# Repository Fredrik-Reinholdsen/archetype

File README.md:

# Archetype

A compact System on Module (SOM) for audio processing and DSP.
It features 6-layer, 5x3 cm PCB, a powerful 550 MHz STM32H7 micro-controller with additional peripherals such as a high fidelity audio CODEC,
SDRAM and flash memory.

The board has two mezzanine connectors on the back, one for analog signals and one for digital.
Many of the STM32 peripherals are wired to and accesible via the mezzanine connectors, including SPI, I2C, UART, CAN, ADC inputs.

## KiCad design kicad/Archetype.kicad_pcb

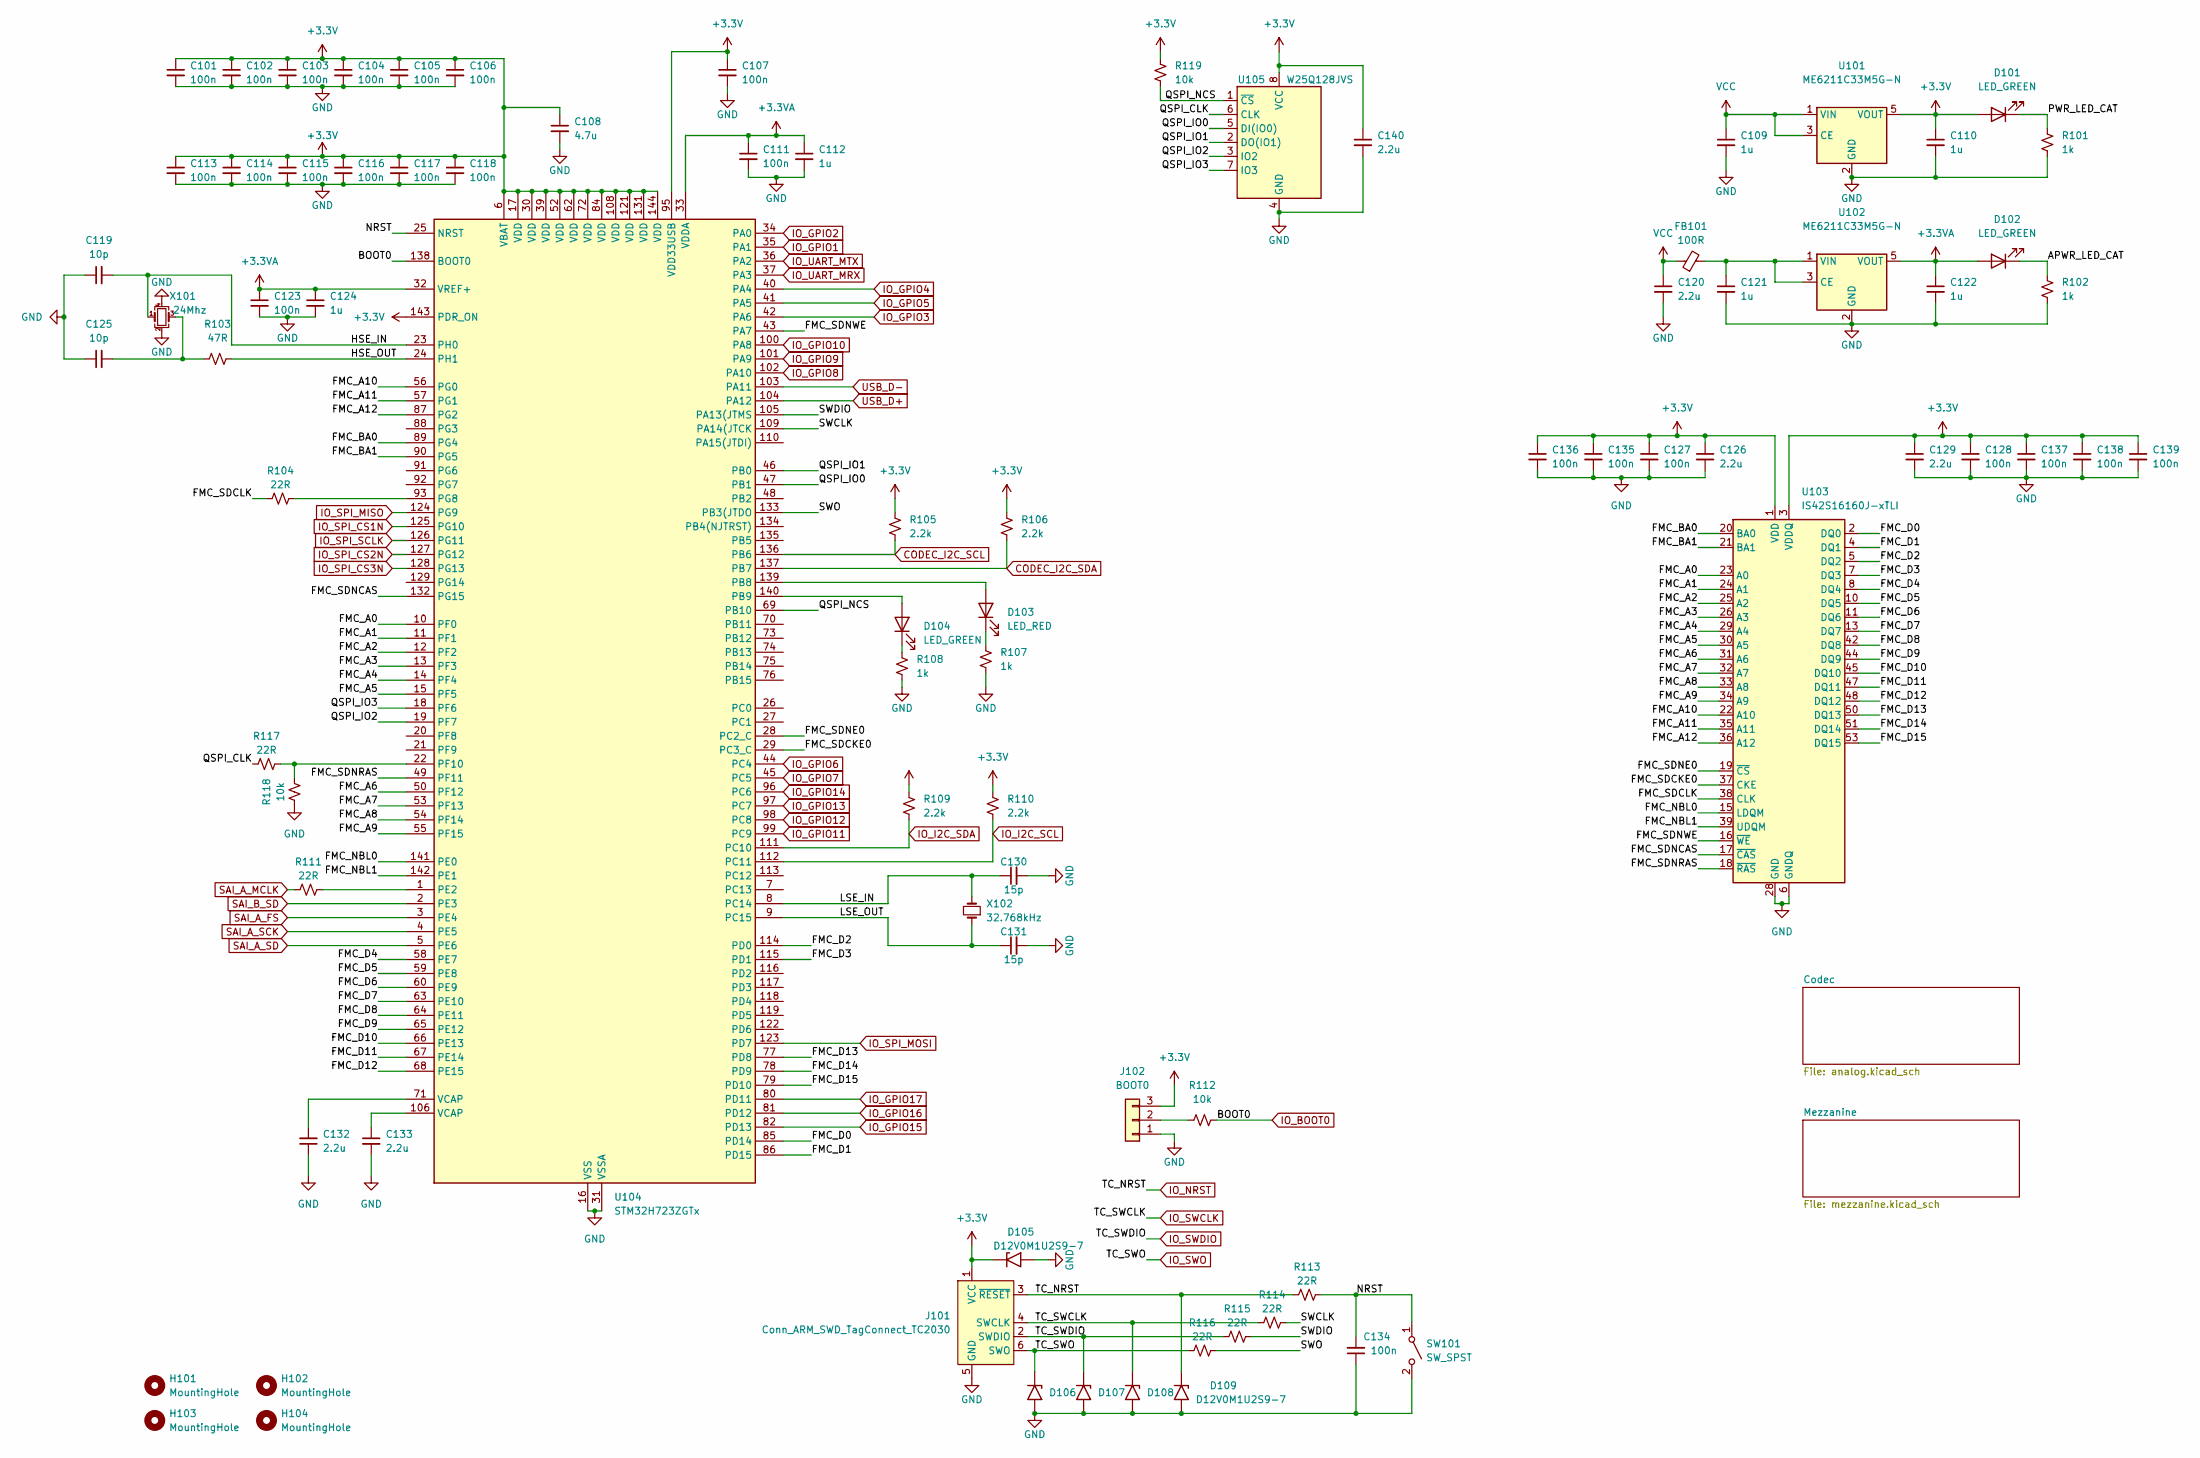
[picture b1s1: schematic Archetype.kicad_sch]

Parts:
C101, C102, C103, C104, C105, C106, C107, C111, C113, C114, C115, C116, C117, C118, C123, C127, C128, C134, C135, C136, C137, C138, C139: 100n; C_0402_1005Metric
C108: 4.7u; C_0402_1005Metric
C109, C110, C112, C121, C122, C124: 1u; C_0402_1005Metric
C119, C125: 10p; C_0603_1608Metric
C120, C126, C129, C132, C133, C140: 2.2u; C_0402_1005Metric
C130, C131: 15p; C_0603_1608Metric
D101, D102, D104: LED_GREEN; LED_0805_2012Metric
D103: LED_RED; LED_0805_2012Metric
D105, D106, D107, D108, D109: D12V0M1U2S9-7; D_SOD-923
FB101: 100R; R_0805_2012Metric
H101, H102, H103, H104: MountingHole; MountingHole_2.2mm_M2_DIN965
J101: Conn_ARM_SWD_TagConnect_TC2030; Tag-Connect_TC2030-IDC-FP_2x03_P1.27mm_Vertical
J102: BOOT0; PinSocket_1x03_P2.54mm_Vertical
R101, R102, R107, R108: 1k; R_0402_1005Metric
R103: 47R; R_0402_1005Metric
R104, R111, R113, R114, R115, R116, R117: 22R; R_0402_1005Metric
R105, R106, R109, R110: 2.2k; R_0402_1005Metric
R112, R118, R119: 10k; R_0402_1005Metric
SW101: SW_SPST; SPST_TS-1187A-B-A-B
U101, U102: ME6211C33M5G-N; SOT-23-5
U103: IS42S16160J-xTLI; TSOP-II-54_22.2x10.16mm_P0.8mm
U104: STM32H723ZGTx; LQFP-144_20x20mm_P0.5mm
U105: W25Q128JVS; SOIC-8_5.23x5.23mm_P1.27mm
X101: 24Mhz; Crystal_SMD_3225-4Pin_3.2x2.5mm
X102: 32.768kHz; SMD_3215-2Pin

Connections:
+3.3V: C101.1, C102.1, C103.1, C104.1, C105.1, C106.1, C107.1, C108.1, C110.1, C113.1, C114.1, C115.1, C116.1, C117.1, C118.1, C126.1, C127.1, C128.1, C129.1, C135.1, C136.1, C137.1, C138.1, C139.1, C140.1, D101.2 (A), D105.1 (A1), J101.1 (VCC), J102.3, R105.1, R106.1, R109.1, R110.1, R119.1, U101.5 (VOUT), U103.1 (VDD), U103.3 (VDDQ), U103.9 (VDDQ), U103.14 (VDD), U103.27 (VDD), U103.43 (VDDQ), U103.49 (VDDQ), U104.6 (VBAT), U104.17 (VDD), U104.30 (VDD), U104.39 (VDD), U104.52 (VDD), U104.62 (VDD), U104.72 (VDD), U104.84 (VDD), U104.95 (VDD33USB), U104.108 (VDD), U104.121 (VDD), U104.131 (VDD), U104.143 (PDR_ON), U104.144 (VDD), U105.8 (VCC); also elsewhere on the board
+3.3VA: C111.1, C112.1, C122.1, C123.1, C124.1, D102.2 (A), U102.5 (VOUT), U104.32 (VREF+), U104.33 (VDDA); also elsewhere on the board
/APWR_LED_CAT: D102.1 (K), R102.1
/FMC_A0: U103.23 (A0), U104.10 (PF0)
/FMC_A1: U103.24 (A1), U104.11 (PF1)
/FMC_A2: U103.25 (A2), U104.12 (PF2)
/FMC_A3: U103.26 (A3), U104.13 (PF3)
/FMC_A4: U103.29 (A4), U104.14 (PF4)
/FMC_A5: U103.30 (A5), U104.15 (PF5)
/FMC_A6: U103.31 (A6), U104.50 (PF12)
/FMC_A7: U103.32 (A7), U104.53 (PF13)
/FMC_A8: U103.33 (A8), U104.54 (PF14)
/FMC_A9: U103.34 (A9), U104.55 (PF15)
/FMC_A10: U103.22 (A10), U104.56 (PG0)
/FMC_A11: U103.35 (A11), U104.57 (PG1)
/FMC_A12: U103.36 (A12), U104.87 (PG2)
/FMC_BA0: U103.20 (BA0), U104.89 (PG4)
/FMC_BA1: U103.21 (BA1), U104.90 (PG5)
/FMC_D0: U103.2 (DQ0), U104.85 (PD14)
/FMC_D1: U103.4 (DQ1), U104.86 (PD15)
/FMC_D2: U103.5 (DQ2), U104.114 (PD0)
/FMC_D3: U103.7 (DQ3), U104.115 (PD1)
/FMC_D4: U103.8 (DQ4), U104.58 (PE7)
/FMC_D5: U103.10 (DQ5), U104.59 (PE8)
/FMC_D6: U103.11 (DQ6), U104.60 (PE9)
/FMC_D7: U103.13 (DQ7), U104.63 (PE10)
/FMC_D8: U103.42 (DQ8), U104.64 (PE11)
/FMC_D9: U103.44 (DQ9), U104.65 (PE12)
/FMC_D10: U103.45 (DQ10), U104.66 (PE13)
/FMC_D11: U103.47 (DQ11), U104.67 (PE14)
/FMC_D12: U103.48 (DQ12), U104.68 (PE15)
/FMC_D13: U103.50 (DQ13), U104.77 (PD8)
/FMC_D14: U103.51 (DQ14), U104.78 (PD9)
/FMC_D15: U103.53 (DQ15), U104.79 (PD10)
/FMC_NBL0: U103.15 (LDQM), U104.141 (PE0)
/FMC_NBL1: U103.39 (UDQM), U104.142 (PE1)
/FMC_SDCKE0: U103.37 (CKE), U104.29 (PC3_C)
/FMC_SDCLK: R104.2, U103.38 (CLK)
/FMC_SDNCAS: U103.17 (~CAS), U104.132 (PG15)
/FMC_SDNE0: U103.19 (~CS), U104.28 (PC2_C)
/FMC_SDNRAS: U103.18 (~RAS), U104.49 (PF11)
/FMC_SDNWE: U103.16 (~WE), U104.43 (PA7)
/HSE_IN: C119.2, U104.23 (PH0), X101.1
/HSE_OUT: R103.1, U104.24 (PH1)
/LSE_IN: C130.1, U104.8 (PC14), X102.2
/LSE_OUT: C131.1, U104.9 (PC15), X102.1
/NRST: C134.2, R113.2, SW101.1 (A), U104.25 (NRST)
/PWR_LED_CAT: D101.1 (K), R101.1
/QSPI_CLK: R117.2, U105.6 (CLK)
/QSPI_IO0: U104.47 (PB1), U105.5 (DI(IO0))
/QSPI_IO1: U104.46 (PB0), U105.2 (DO(IO1))
/QSPI_IO2: U104.19 (PF7), U105.3 (IO2)
/QSPI_IO3: U104.18 (PF6), U105.7 (IO3)
/QSPI_NCS: R119.2, U104.69 (PB10), U105.1 (~CS)
/SWCLK: R114.2, U104.109 (PA14(JTCK)
/SWDIO: R115.2, U104.105 (PA13(JTMS)
/SWO: R116.2, U104.133 (PB3(JTDO)
CODEC_I2C_SCL: R105.2, U104.136 (PB6); also elsewhere on the board
CODEC_I2C_SDA: R106.2, U104.137 (PB7); also elsewhere on the board
GND: C101.2, C102.2, C103.2, C104.2, C105.2, C106.2, C107.2, C108.2, C109.2, C110.2, C111.2, C112.2, C113.2, C114.2, C115.2, C116.2, C117.2, C118.2, C119.1, C120.2, C121.2, C122.2, C123.2, C124.2, C125.1, C126.2, C127.2, C128.2, C129.2, C130.2, C131.2, C132.1, C133.2, C134.1, C135.2, C136.2, C137.2, C138.2, C139.2, C140.2, D105.2 (A2), D106.2 (A2), D107.2 (A2), D108.2 (A2), D109.2 (A2), J101.5 (GND), J102.1, R101.2, R102.2, R107.2, R108.2, R118.2, SW101.2 (B), U101.2 (GND), U102.2 (GND), U103.6 (GNDQ), U103.12 (GNDQ), U103.28 (GND), U103.41 (GND), U103.46 (GNDQ), U103.52 (GNDQ), U103.54 (GND), U104.16 (VSS), U104.31 (VSSA), U104.38 (VSS), U104.51 (VSS), U104.61 (VSS), U104.83 (VSS), U104.94 (VSS), U104.107 (VSS), U104.120 (VSS), U104.130 (VSS), U105.4 (GND), X101.2, X101.4; also elsewhere on the board
IO_BOOT0: R112.2, U104.138 (BOOT0); also elsewhere on the board
IO_GPIO1: U104.35 (PA1); also elsewhere on the board
IO_GPIO2: U104.34 (PA0); also elsewhere on the board
IO_GPIO3: U104.42 (PA6); also elsewhere on the board
IO_GPIO4: U104.40 (PA4); also elsewhere on the board
IO_GPIO5: U104.41 (PA5); also elsewhere on the board
IO_GPIO6: U104.44 (PC4); also elsewhere on the board
IO_GPIO7: U104.45 (PC5); also elsewhere on the board
IO_GPIO8: U104.102 (PA10); also elsewhere on the board
IO_GPIO9: U104.101 (PA9); also elsewhere on the board
IO_GPIO10: U104.100 (PA8); also elsewhere on the board
IO_GPIO11: U104.99 (PC9); also elsewhere on the board
IO_GPIO12: U104.98 (PC8); also elsewhere on the board
IO_GPIO13: U104.97 (PC7); also elsewhere on the board
IO_GPIO14: U104.96 (PC6); also elsewhere on the board
IO_GPIO15: U104.82 (PD13); also elsewhere on the board
IO_GPIO16: U104.81 (PD12); also elsewhere on the board
IO_GPIO17: U104.80 (PD11); also elsewhere on the board
IO_I2C_SCL: R110.2, U104.112 (PC11); also elsewhere on the board
IO_I2C_SDA: R109.2, U104.111 (PC10); also elsewhere on the board
IO_NRST: D109.1 (A1), J101.3 (~RESET), R113.1; also elsewhere on the board
IO_SPI_CS1N: U104.125 (PG10); also elsewhere on the board
IO_SPI_CS2N: U104.127 (PG12); also elsewhere on the board
IO_SPI_CS3N: U104.128 (PG13); also elsewhere on the board
IO_SPI_MISO: U104.124 (PG9); also elsewhere on the board
IO_SPI_MOSI: U104.123 (PD7); also elsewhere on the board
IO_SPI_SCLK: U104.126 (PG11); also elsewhere on the board
IO_SWCLK: D108.1 (A1), J101.4 (SWCLK), R114.1; also elsewhere on the board
IO_SWDIO: D107.1 (A1), J101.2 (SWDIO), R115.1; also elsewhere on the board
IO_SWO: D106.1 (A1), J101.6 (SWO), R116.1; also elsewhere on the board
IO_UART_MRX: U104.37 (PA3); also elsewhere on the board
IO_UART_MTX: U104.36 (PA2); also elsewhere on the board
unnamed: C125.2, R103.2, X101.3
unnamed: C132.2, U104.71 (VCAP)
unnamed: C133.1, U104.106 (VCAP)
unnamed: D103.2 (A), U104.139 (PB8)
unnamed: D103.1 (K), R107.1
unnamed: D104.2 (A), U104.140 (PB9)
unnamed: D104.1 (K), R108.1
unnamed: J102.2, R112.1
unnamed: C121.1, FB101.2, U102.1 (VIN), U102.3 (CE)
unnamed: R111.1, U104.1 (PE2)
unnamed: R117.1, R118.1, U104.22 (PF10)
unnamed: R104.1, U104.93 (PG8)
SAI_A_FS: U104.3 (PE4); also elsewhere on the board
SAI_A_MCLK: R111.2; also elsewhere on the board
SAI_A_SCK: U104.4 (PE5); also elsewhere on the board
SAI_A_SD: U104.5 (PE6); also elsewhere on the board
SAI_B_SD: U104.2 (PE3); also elsewhere on the board
USB_D+: U104.104 (PA12); also elsewhere on the board
USB_D-: U104.103 (PA11); also elsewhere on the board
VCC: C109.1, C120.1, FB101.1, U101.1 (VIN), U101.3 (CE); also elsewhere on the board

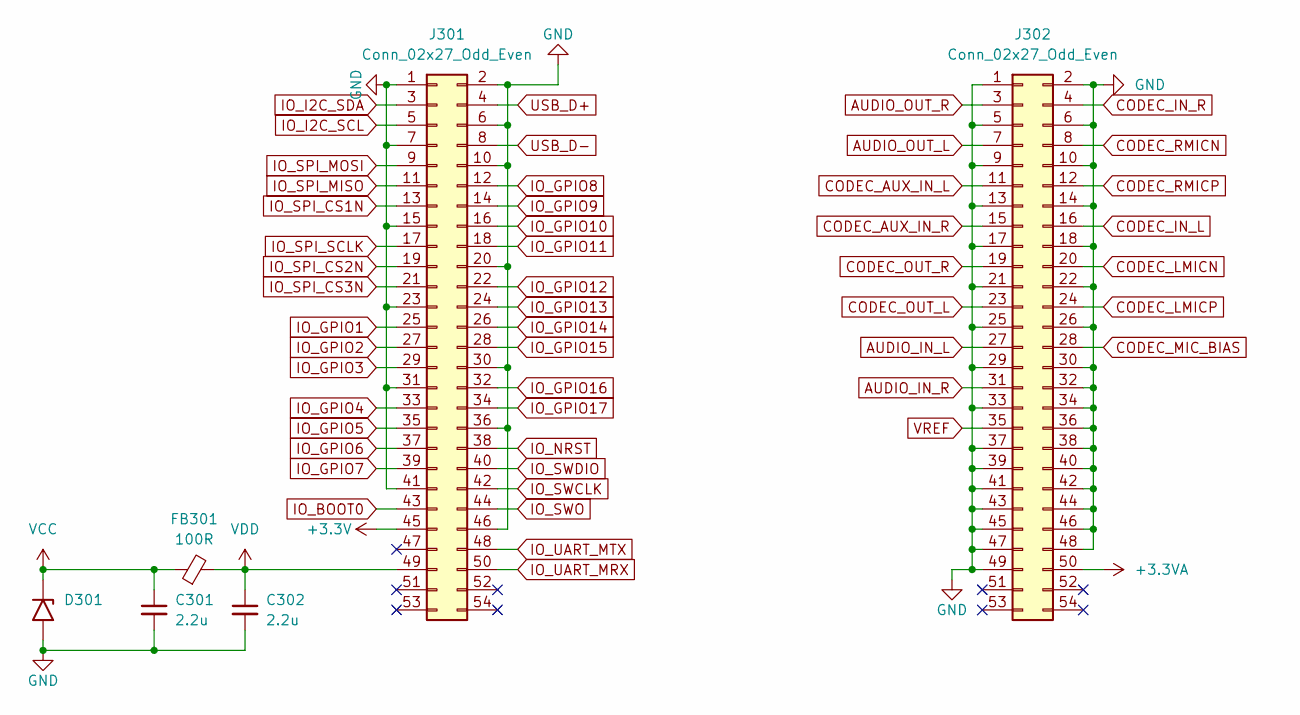
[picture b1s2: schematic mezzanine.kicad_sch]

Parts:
C301, C302: 2.2u; C_0402_1005Metric
D301: D12V0M1U2S9-7; D_SOD-923
FB301: 100R; R_0805_2012Metric
J301, J302: Conn_02x27_Odd_Even; DF40C-50DP-0.4V

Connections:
+3.3V: J301.45; also elsewhere on the board
+3.3VA: J302.50; also elsewhere on the board
AUDIO_IN_L: J302.27; also elsewhere on the board
AUDIO_IN_R: J302.31; also elsewhere on the board
AUDIO_OUT_L: J302.7; also elsewhere on the board
AUDIO_OUT_R: J302.3; also elsewhere on the board
CODEC_AUX_IN_L: J302.11; also elsewhere on the board
CODEC_AUX_IN_R: J302.15; also elsewhere on the board
CODEC_IN_L: J302.16; also elsewhere on the board
CODEC_IN_R: J302.4; also elsewhere on the board
CODEC_LMICN: J302.20; also elsewhere on the board
CODEC_LMICP: J302.24; also elsewhere on the board
CODEC_MIC_BIAS: J302.28; also elsewhere on the board
CODEC_OUT_L: J302.23; also elsewhere on the board
CODEC_OUT_R: J302.19; also elsewhere on the board
CODEC_RMICN: J302.8; also elsewhere on the board
CODEC_RMICP: J302.12; also elsewhere on the board
GND: C301.2, C302.2, D301.2 (A2), J301.1, J301.2, J301.6, J301.7, J301.10, J301.15, J301.20, J301.23, J301.30, J301.31, J301.36, J301.41, J301.46, J302.1, J302.2, J302.5, J302.6, J302.9, J302.10, J302.13, J302.14, J302.17, J302.18, J302.21, J302.22, J302.25, J302.26, J302.29, J302.30, J302.32, J302.33, J302.34, J302.36, J302.37, J302.38, J302.39, J302.40, J302.41, J302.42, J302.43, J302.44, J302.45, J302.46, J302.47, J302.48, J302.49; also elsewhere on the board
IO_BOOT0: J301.43; also elsewhere on the board
IO_GPIO1: J301.25; also elsewhere on the board
IO_GPIO2: J301.27; also elsewhere on the board
IO_GPIO3: J301.29; also elsewhere on the board
IO_GPIO4: J301.33; also elsewhere on the board
IO_GPIO5: J301.35; also elsewhere on the board
IO_GPIO6: J301.37; also elsewhere on the board
IO_GPIO7: J301.39; also elsewhere on the board
IO_GPIO8: J301.12; also elsewhere on the board
IO_GPIO9: J301.14; also elsewhere on the board
IO_GPIO10: J301.16; also elsewhere on the board
IO_GPIO11: J301.18; also elsewhere on the board
IO_GPIO12: J301.22; also elsewhere on the board
IO_GPIO13: J301.24; also elsewhere on the board
IO_GPIO14: J301.26; also elsewhere on the board
IO_GPIO15: J301.28; also elsewhere on the board
IO_GPIO16: J301.32; also elsewhere on the board
IO_GPIO17: J301.34; also elsewhere on the board
IO_I2C_SCL: J301.5; also elsewhere on the board
IO_I2C_SDA: J301.3; also elsewhere on the board
IO_NRST: J301.38; also elsewhere on the board
IO_SPI_CS1N: J301.13; also elsewhere on the board
IO_SPI_CS2N: J301.19; also elsewhere on the board
IO_SPI_CS3N: J301.21; also elsewhere on the board
IO_SPI_MISO: J301.11; also elsewhere on the board
IO_SPI_MOSI: J301.9; also elsewhere on the board
IO_SPI_SCLK: J301.17; also elsewhere on the board
IO_SWCLK: J301.42; also elsewhere on the board
IO_SWDIO: J301.40; also elsewhere on the board
IO_SWO: J301.44; also elsewhere on the board
IO_UART_MRX: J301.50; also elsewhere on the board
IO_UART_MTX: J301.48; also elsewhere on the board
USB_D+: J301.4; also elsewhere on the board
USB_D-: J301.8; also elsewhere on the board
VCC: C301.1, D301.1 (A1), FB301.1; also elsewhere on the board
VDD: C302.1, FB301.2, J301.49
VREF: J302.35; also elsewhere on the board

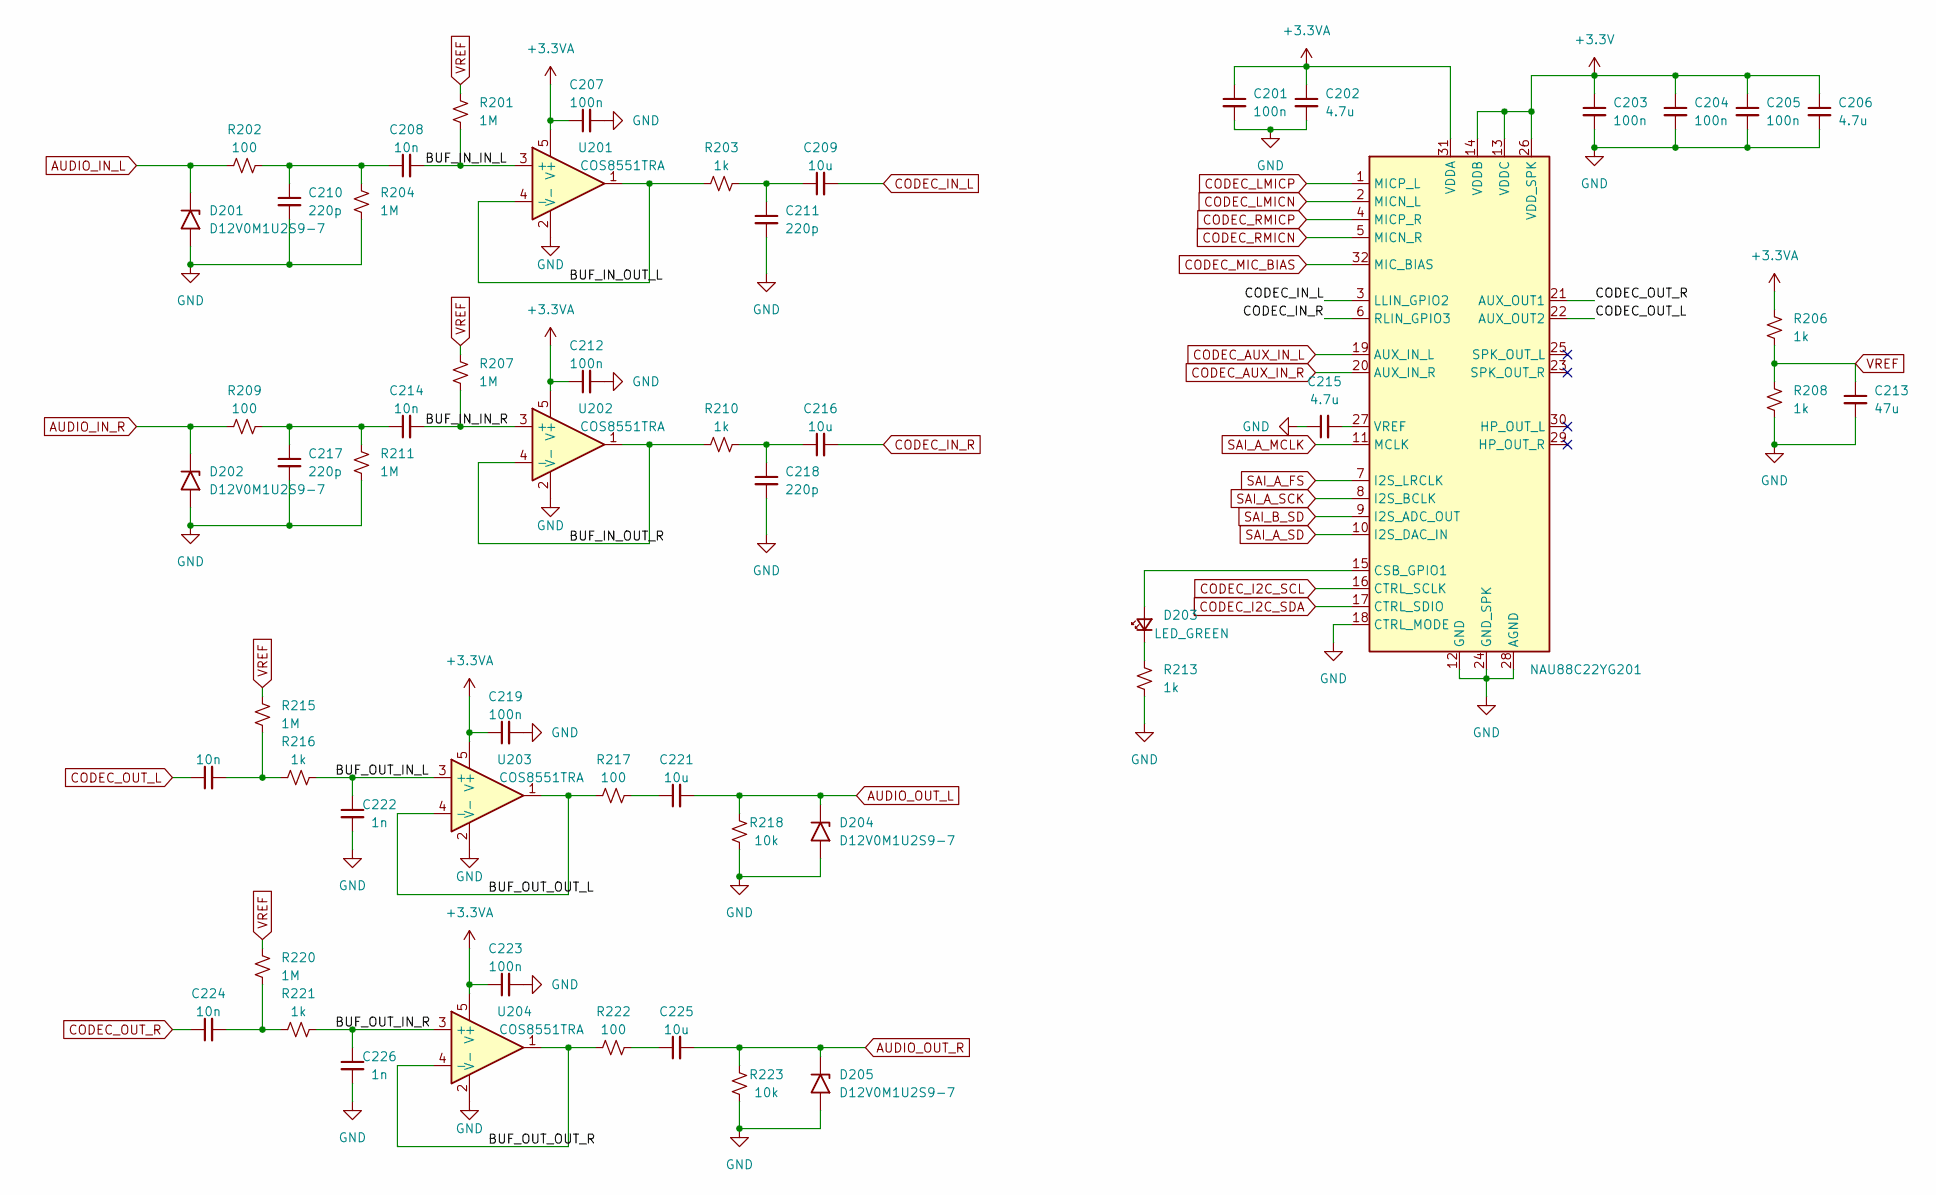
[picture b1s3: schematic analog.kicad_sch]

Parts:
C201, C203, C204, C205, C207, C212, C219, C223: 100n; C_0402_1005Metric
C202, C206, C215: 4.7u; C_0402_1005Metric
C208, C214, C220, C224: 10n; C_0402_1005Metric
C209, C216, C221, C225: 10u; C_0402_1005Metric
C210, C211, C217, C218: 220p; C_0402_1005Metric
C213: 47u; C_0402_1005Metric
C222, C226: 1n; C_0402_1005Metric
D201, D202, D204, D205: D12V0M1U2S9-7; D_SOD-923
D203: LED_GREEN; LED_0805_2012Metric
NAU88C22YG201: VQFN-32-1EP_5x5mm_P0.5mm_EP3.5x3.5mm
R201, R204, R207, R211, R215, R220: 1M; R_0402_1005Metric
R202, R209, R217, R222: 100; R_0402_1005Metric
R203, R206, R208, R210, R213, R216, R221: 1k; R_0402_1005Metric
R218, R223: 10k; R_0402_1005Metric
U201, U202, U203, U204: COS8551TRA; SOT-23-5

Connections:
+3.3V: C203.1, C204.1, C205.1, C206.1, NAU88C22YG201.13 (VDDC), NAU88C22YG201.14 (VDDB), NAU88C22YG201.26 (VDD_SPK); also elsewhere on the board
+3.3VA: C201.1, C202.1, C207.1, C212.1, C219.1, C223.1, NAU88C22YG201.31 (VDDA), R206.2, U201.5 (V+), U202.5 (V+), U203.5 (V+), U204.5 (V+); also elsewhere on the board
/Codec/BUF_IN_IN_L: C208.2, R201.1, U201.3 (+)
/Codec/BUF_IN_IN_R: C214.2, R207.1, U202.3 (+)
/Codec/BUF_IN_OUT_L: R203.2, U201.1, U201.4 (-)
/Codec/BUF_IN_OUT_R: R210.2, U202.1, U202.4 (-)
/Codec/BUF_OUT_IN_L: C222.1, R216.1, U203.3 (+)
/Codec/BUF_OUT_IN_R: C226.1, R221.1, U204.3 (+)
/Codec/BUF_OUT_OUT_L: R217.2, U203.1, U203.4 (-)
/Codec/BUF_OUT_OUT_R: R222.2, U204.1, U204.4 (-)
AUDIO_IN_L: D201.1 (A1), R202.1; also elsewhere on the board
AUDIO_IN_R: D202.1 (A1), R209.1; also elsewhere on the board
AUDIO_OUT_L: C221.2, D204.1 (A1), R218.2; also elsewhere on the board
AUDIO_OUT_R: C225.2, D205.1 (A1), R223.2; also elsewhere on the board
CODEC_AUX_IN_L: NAU88C22YG201.19 (AUX_IN_L); also elsewhere on the board
CODEC_AUX_IN_R: NAU88C22YG201.20 (AUX_IN_R); also elsewhere on the board
CODEC_I2C_SCL: NAU88C22YG201.16 (CTRL_SCLK); also elsewhere on the board
CODEC_I2C_SDA: NAU88C22YG201.17 (CTRL_SDIO); also elsewhere on the board
CODEC_IN_L: C209.2, NAU88C22YG201.3 (LLIN_GPIO2); also elsewhere on the board
CODEC_IN_R: C216.2, NAU88C22YG201.6 (RLIN_GPIO3); also elsewhere on the board
CODEC_LMICN: NAU88C22YG201.2 (MICN_L); also elsewhere on the board
CODEC_LMICP: NAU88C22YG201.1 (MICP_L); also elsewhere on the board
CODEC_MIC_BIAS: NAU88C22YG201.32 (MIC_BIAS); also elsewhere on the board
CODEC_OUT_L: C220.1, NAU88C22YG201.22 (AUX_OUT2); also elsewhere on the board
CODEC_OUT_R: C224.1, NAU88C22YG201.21 (AUX_OUT1); also elsewhere on the board
CODEC_RMICN: NAU88C22YG201.5 (MICN_R); also elsewhere on the board
CODEC_RMICP: NAU88C22YG201.4 (MICP_R); also elsewhere on the board
GND: C201.2, C202.2, C203.2, C204.2, C205.2, C206.2, C207.2, C210.2, C211.2, C212.2, C213.2, C215.1, C217.2, C218.2, C219.2, C222.2, C223.2, C226.2, D201.2 (A2), D202.2 (A2), D204.2 (A2), D205.2 (A2), NAU88C22YG201.12 (GND), NAU88C22YG201.18 (CTRL_MODE), NAU88C22YG201.24 (GND_SPK), NAU88C22YG201.28 (AGND), NAU88C22YG201.33 (GND), R204.1, R208.1, R211.1, R213.2, R218.1, R223.1, U201.2 (V-), U202.2 (V-), U203.2 (V-), U204.2 (V-); also elsewhere on the board
unnamed: C208.1, C210.1, R202.2, R204.2
unnamed: C209.1, C211.1, R203.1
unnamed: C214.1, C217.1, R209.2, R211.2
unnamed: C216.1, C218.1, R210.1
unnamed: C220.2, R215.1, R216.2
unnamed: C221.1, R217.1
unnamed: C224.2, R220.1, R221.2
unnamed: C225.1, R222.1
unnamed: D203.2 (A), NAU88C22YG201.15 (CSB_GPIO1)
unnamed: D203.1 (K), R213.1
unnamed: C215.2, NAU88C22YG201.27 (VREF)
SAI_A_FS: NAU88C22YG201.7 (I2S_LRCLK); also elsewhere on the board
SAI_A_MCLK: NAU88C22YG201.11 (MCLK); also elsewhere on the board
SAI_A_SCK: NAU88C22YG201.8 (I2S_BCLK); also elsewhere on the board
SAI_A_SD: NAU88C22YG201.10 (I2S_DAC_IN); also elsewhere on the board
SAI_B_SD: NAU88C22YG201.9 (I2S_ADC_OUT); also elsewhere on the board
VREF: C213.1, R201.2, R206.1, R207.2, R208.2, R215.2, R220.2; also elsewhere on the board

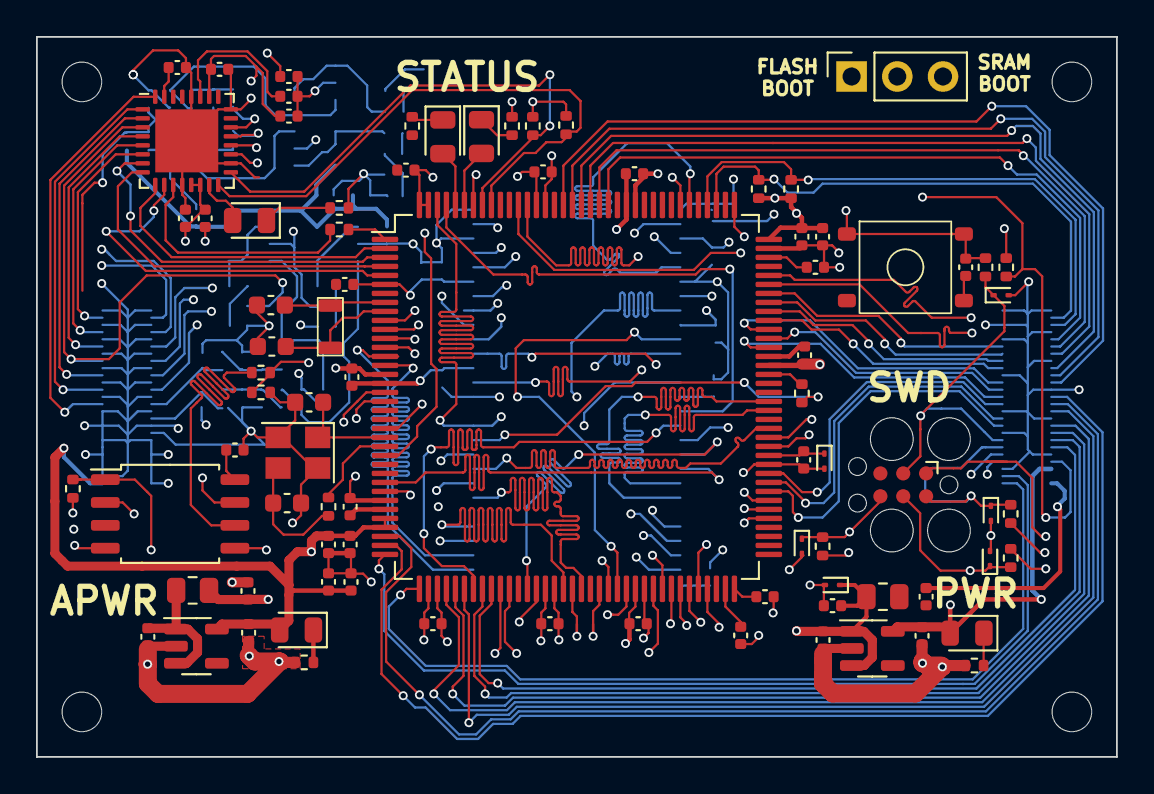
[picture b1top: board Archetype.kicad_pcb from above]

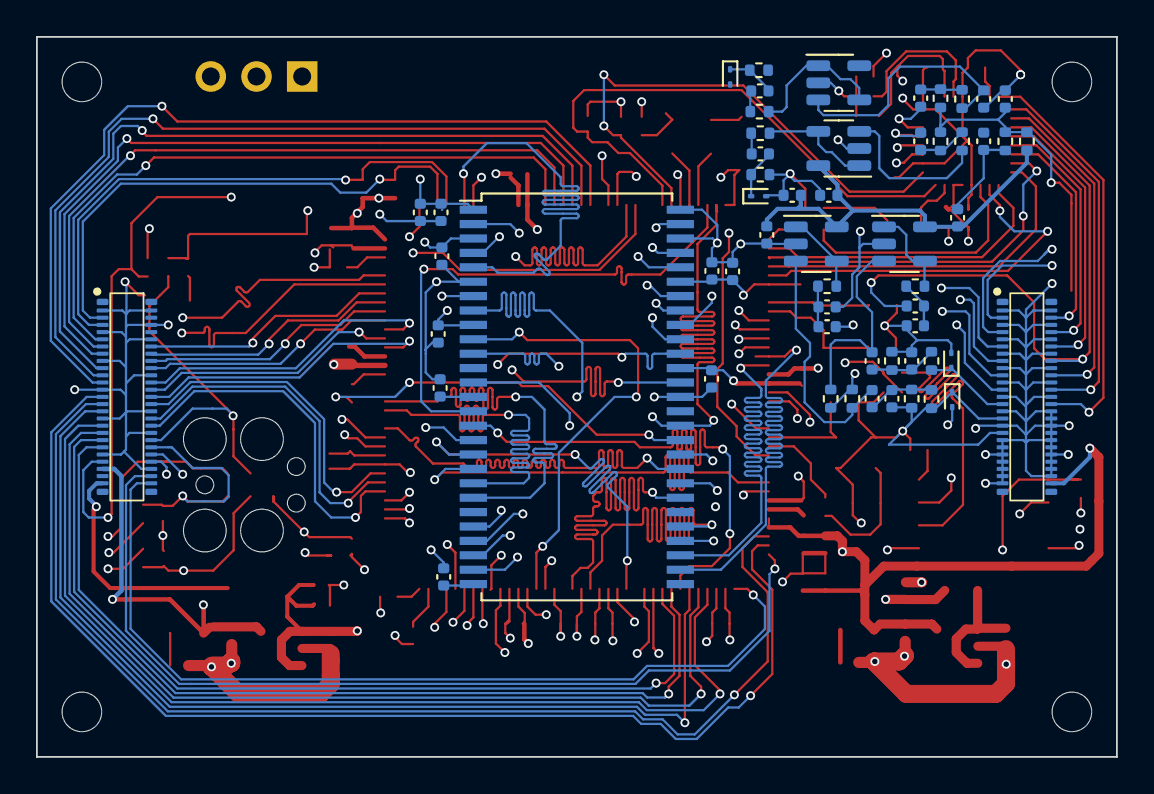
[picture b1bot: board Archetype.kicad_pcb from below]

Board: 6 copper layers, 60.0 x 40.0 mm, 144 parts (57 on the bottom side), 148 nets.

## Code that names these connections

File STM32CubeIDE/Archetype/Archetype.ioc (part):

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Mcu.Name=STM32H723ZGTx
Mcu.Package=LQFP144
Mcu.UserName=STM32H723ZGTx
PA11.Mode=Device_Only_FS
PA11.Signal=USB_OTG_HS_DM
PA12.Mode=Device_Only_FS
PA12.Signal=USB_OTG_HS_DP
PA13(JTMS/SWDIO).Mode=Trace_Asynchronous_SW
PA13(JTMS/SWDIO).Signal=DEBUG_JTMS-SWDIO
PA14(JTCK/SWCLK).Mode=Trace_Asynchronous_SW
PA14(JTCK/SWCLK).Signal=DEBUG_JTCK-SWCLK
PA2.Mode=Asynchronous
PA2.Signal=USART2_TX
PA3.Mode=Asynchronous
PA3.Signal=USART2_RX
PA4.Signal=ADCx_INP18
PA5.Signal=ADCx_INP19
PA6.Signal=ADCx_INP3
PA7.Signal=FMC_SDNWE
PB0.Mode=OCTOSPI1_IOL_Port1L
PB0.Signal=OCTOSPIM_P1_IO1
PB1.Mode=OCTOSPI1_IOL_Port1L
PB1.Signal=OCTOSPIM_P1_IO0
PB10.Mode=OCTOSPI1_Port1_NCS
PB10.Signal=OCTOSPIM_P1_NCS
PB3(JTDO/TRACESWO).Mode=Trace_Asynchronous_SW
PB3(JTDO/TRACESWO).Signal=DEBUG_JTDO-SWO
PB6.Mode=I2C
PB6.Signal=I2C1_SCL
PB7.Mode=I2C
PB7.Signal=I2C1_SDA
PC10.Mode=I2C
PC10.Signal=I2C5_SDA
PC11.Mode=I2C
PC11.Signal=I2C5_SCL
PC14-OSC32_IN.Mode=LSE-External-Oscillator
PC14-OSC32_IN.Signal=RCC_OSC32_IN
PC15-OSC32_OUT.Mode=LSE-External-Oscillator
PC15-OSC32_OUT.Signal=RCC_OSC32_OUT
PC2_C.Mode=SdramChipSelect1_1
PC2_C.Signal=FMC_SDNE0
PC3_C.Mode=SdramChipSelect1_1
PC3_C.Signal=FMC_SDCKE0
PC4.Signal=ADCx_INP4
PC5.Signal=ADCx_INP8
PC6.Signal=S_TIM3_CH1
PC7.Signal=S_TIM3_CH2
PD0.Signal=FMC_D2_DA2
PD1.Signal=FMC_D3_DA3
PD10.Signal=FMC_D15_DA15
PD12.Mode=FDCAN_Activate
PD12.Signal=FDCAN3_RX
PD13.Mode=FDCAN_Activate
PD13.Signal=FDCAN3_TX
PD14.Signal=FMC_D0_DA0
PD15.Signal=FMC_D1_DA1
PD7.Mode=Full_Duplex_Master
PD7.Signal=SPI1_MOSI
PD8.Signal=FMC_D13_DA13
PD9.Signal=FMC_D14_DA14
PE0.Signal=FMC_NBL0
PE1.Signal=FMC_NBL1
PE10.Signal=FMC_D7_DA7
PE11.Signal=FMC_D8_DA8
PE12.Signal=FMC_D9_DA9
PE13.Signal=FMC_D10_DA10
PE14.Signal=FMC_D11_DA11
PE15.Signal=FMC_D12_DA12
PE2.Mode=SAI_A_MasterWithClock
PE2.Signal=SAI1_MCLK_A
PE3.Mode=SAI_B_Master
PE3.Signal=SAI1_SD_B
PE4.Mode=SAI_A_MasterWithClock
PE4.Signal=SAI1_FS_A
PE5.Mode=SAI_A_MasterWithClock
PE5.Signal=SAI1_SCK_A
PE6.Mode=SAI_A_MasterWithClock
PE6.Signal=SAI1_SD_A
PE7.Signal=FMC_D4_DA4
PE8.Signal=FMC_D5_DA5
PE9.Signal=FMC_D6_DA6
PF0.Signal=FMC_A0
PF1.Signal=FMC_A1
PF10.Mode=O1_P1_CLK
PF10.Signal=OCTOSPIM_P1_CLK
PF11.Signal=FMC_SDNRAS
PF12.Signal=FMC_A6
PF13.Signal=FMC_A7
PF14.Signal=FMC_A8
PF15.Signal=FMC_A9
PF2.Signal=FMC_A2
PF3.Signal=FMC_A3
PF4.Signal=FMC_A4
PF5.Signal=FMC_A5
PF6.Mode=OCTOSPI1_IOL_Port1L
PF6.Signal=OCTOSPIM_P1_IO3
PF7.Mode=OCTOSPI1_IOL_Port1L
PF7.Signal=OCTOSPIM_P1_IO2
PF8.Mode=SAI_B_Master
PF8.Signal=SAI1_SCK_B
PF9.Mode=SAI_B_Master
PF9.Signal=SAI1_FS_B
PG0.Signal=FMC_A10
PG1.Signal=FMC_A11
PG10.Signal=SPI1_NSS
PG11.Mode=Full_Duplex_Master
PG11.Signal=SPI1_SCK
PG12.Signal=GPIO_Output
PG13.Signal=GPIO_Output
PG15.Signal=FMC_SDNCAS
PG2.Signal=FMC_A12
PG4.Signal=FMC_A14_BA0
PG5.Signal=FMC_A15_BA1
PG8.Signal=FMC_SDCLK
PG9.Mode=Full_Duplex_Master
PG9.Signal=SPI1_MISO
PH0-OSC_IN.Mode=HSE-External-Oscillator
PH0-OSC_IN.Signal=RCC_OSC_IN
PH1-OSC_OUT.Mode=HSE-External-Oscillator
PH1-OSC_OUT.Signal=RCC_OSC_OUT
RCC.HSE_VALUE=24000000
RCC.SYSCLKFreq_VALUE=550000000
RCC.SYSCLKSource=RCC_SYSCLKSOURCE_PLLCLK
board=custom

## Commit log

2024-08-11 Added README, PDF of the schematic and image and 3D model of the PCB design.
